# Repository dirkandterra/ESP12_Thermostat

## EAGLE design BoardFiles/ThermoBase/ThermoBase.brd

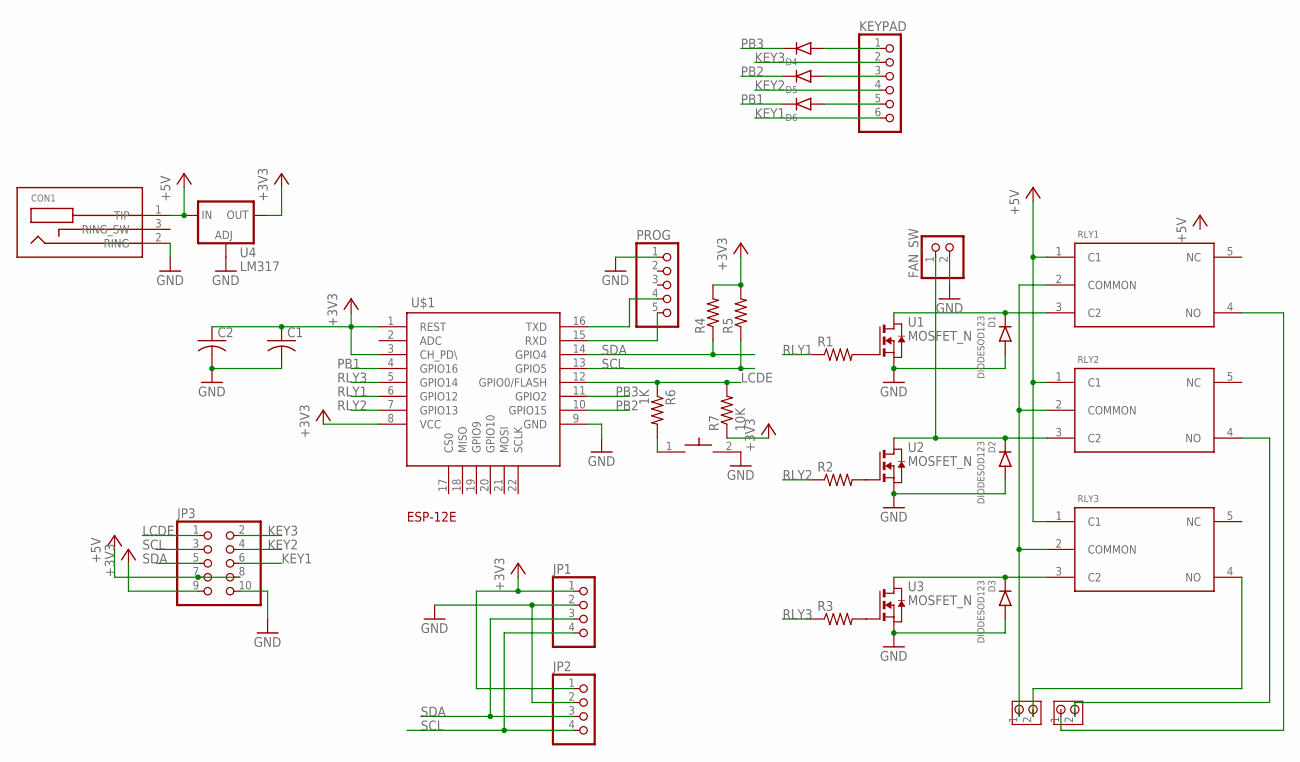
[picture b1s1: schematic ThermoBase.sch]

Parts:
BTN1: FSMSM_SWITCH_6X3.6; SMD-2-SWITCH
C1, C2: C-USC0805; C0805
CON1: BARREL_JACK_3PINPJ-102A_2MM_HOLES; PJ-102A_2MM_HOLES
D1, D2, D3, D4, D5, D6: DIODESOD123; SOD123
FAN_SW: PINHD-1X2; 1X02
H1, H2: TERMBLOCK_5MM_2POS
JP1, JP2: PINHD-1X4; 1X04
JP3: PINHD-2X5; 2X05
KEYPAD: PINHD-1X6; 1X06
PROG: PINHD-1X5; 1X05
R1, R2, R3, R4, R5: R-US_R0805; R0805
R6: 1K; R0805
R7: 10K; R0805
RLY1, RLY2, RLY3: RELAY_JQC-3F; T73_RELAY
U1, U2, U3: MOSFET_N; SOT-23
U4: LM317; SOT223
U$1: ESP-12E

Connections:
+3V3: C1.1, C2.1, JP1.1, JP2.1, JP3.9, R4.2, R5.2, R7.1, U4.2 (OUT), U4.4 (OUT), U$1.1 (REST), U$1.3 (CH_PD\), U$1.8 (VCC)
+5V: CON1.1 (TIP), JP3.7, JP3.8, RLY1.1 (C1), RLY2.1 (C1), RLY3.1 (C1), U4.3 (IN)
GND: BTN1.2, C1.2, C2.2, CON1.2 (RING), D1.1 (A), D2.1 (A), D3.1 (A), FAN_SW.2, JP1.2, JP2.2, JP3.10, PROG.1, U1.2 (S), U2.2 (S), U3.2 (S), U4.1 (ADJ), U$1.9 (GND)
KEY1: JP3.6, KEYPAD.6
KEY2: JP3.4, KEYPAD.4
KEY3: JP3.2, KEYPAD.2
LCDE: JP3.1, R6.1, R7.2, U$1.12 (GPIO0/FLASH)
unnamed: PROG.5, U$1.15 (RXD)
unnamed: PROG.4, U$1.16 (TXD)
unnamed: H2.1, RLY1.4 (NO)
unnamed: R1.2, U1.1 (G)
unnamed: R2.2, U2.1 (G)
unnamed: R3.2, U3.1 (G)
unnamed: D1.2 (C), RLY1.3 (C2), U1.3 (D)
unnamed: H2.2, RLY2.4 (NO)
unnamed: D2.2 (C), FAN_SW.1, RLY2.3 (C2), U2.3 (D)
unnamed: D3.2 (C), RLY3.3 (C2), U3.3 (D)
unnamed: H1.1, RLY1.2 (COMMON), RLY2.2 (COMMON), RLY3.2 (COMMON)
unnamed: H1.2, RLY3.4 (NO)
unnamed: D4.1 (A), KEYPAD.1
unnamed: D5.1 (A), KEYPAD.3
unnamed: D6.1 (A), KEYPAD.5
unnamed: BTN1.1, R6.2
PB1: D6.2 (C), U$1.4 (GPIO16)
PB2: D5.2 (C), U$1.10 (GPIO15)
PB3: D4.2 (C), U$1.11 (GPIO2)
RLY1: R1.1, U$1.6 (GPIO12)
RLY2: R2.1, U$1.7 (GPIO13)
RLY3: R3.1, U$1.5 (GPIO14)
SCL: JP1.4, JP2.4, JP3.3, R5.1, U$1.13 (GPIO5)
SDA: JP1.3, JP2.3, JP3.5, R4.1, U$1.14 (GPIO4)

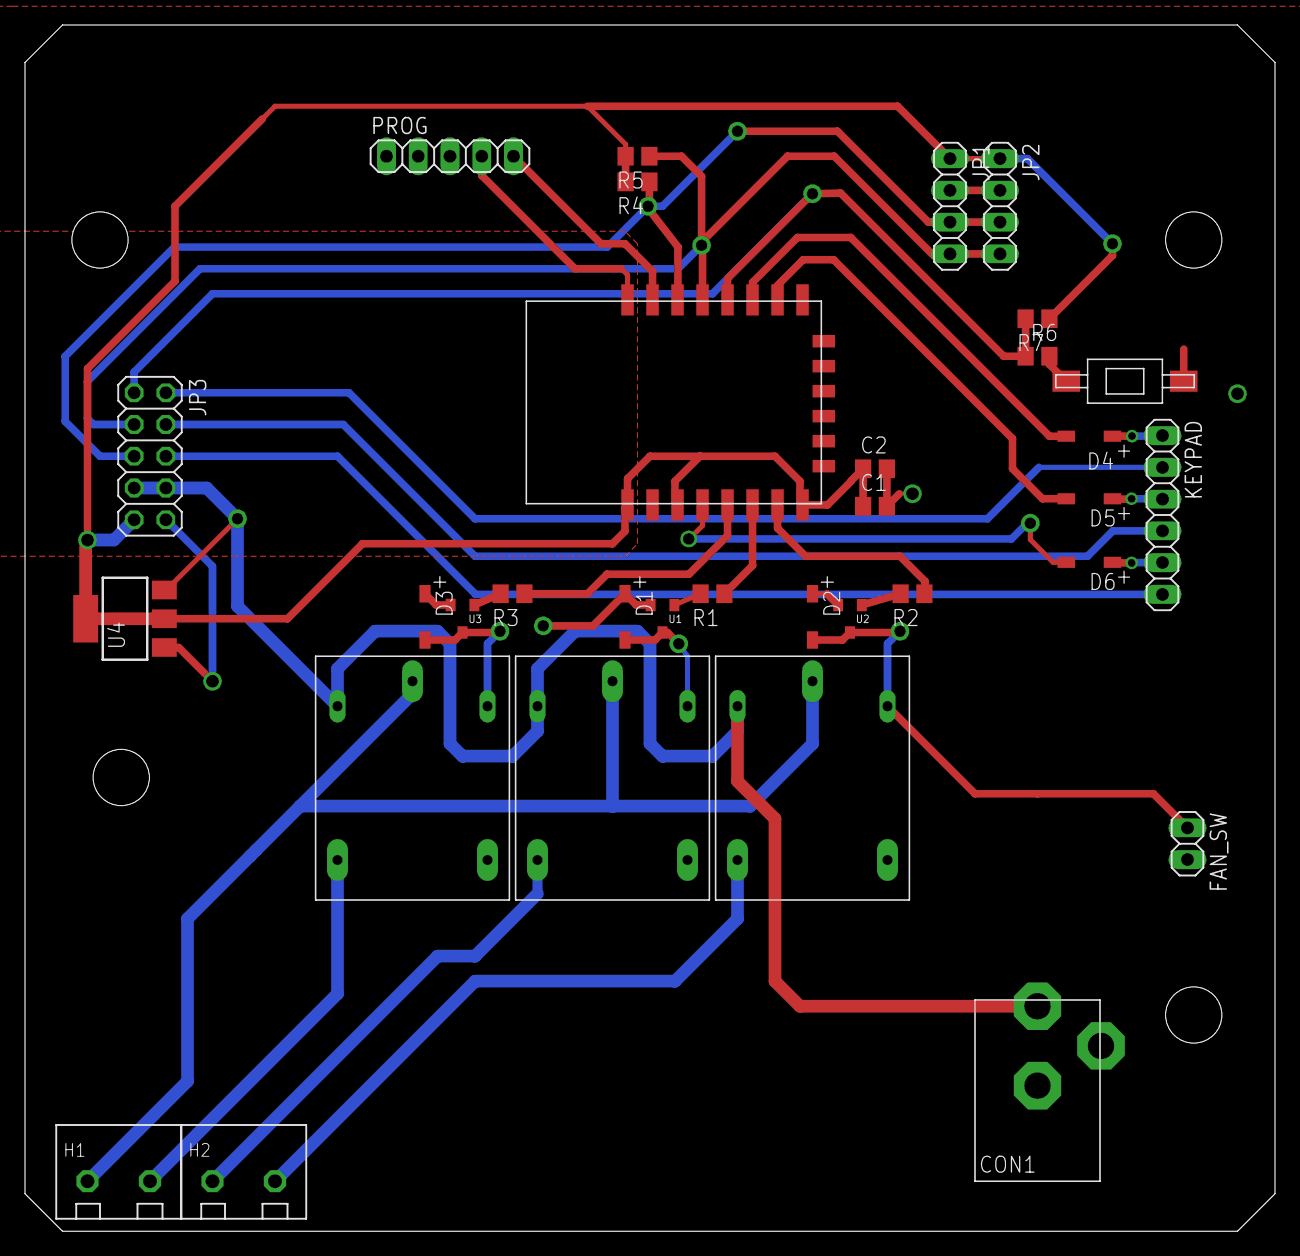
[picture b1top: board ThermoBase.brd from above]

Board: 2 copper layers, 100.0 x 96.5 mm, 33 parts (0 on the bottom side), 31 nets.

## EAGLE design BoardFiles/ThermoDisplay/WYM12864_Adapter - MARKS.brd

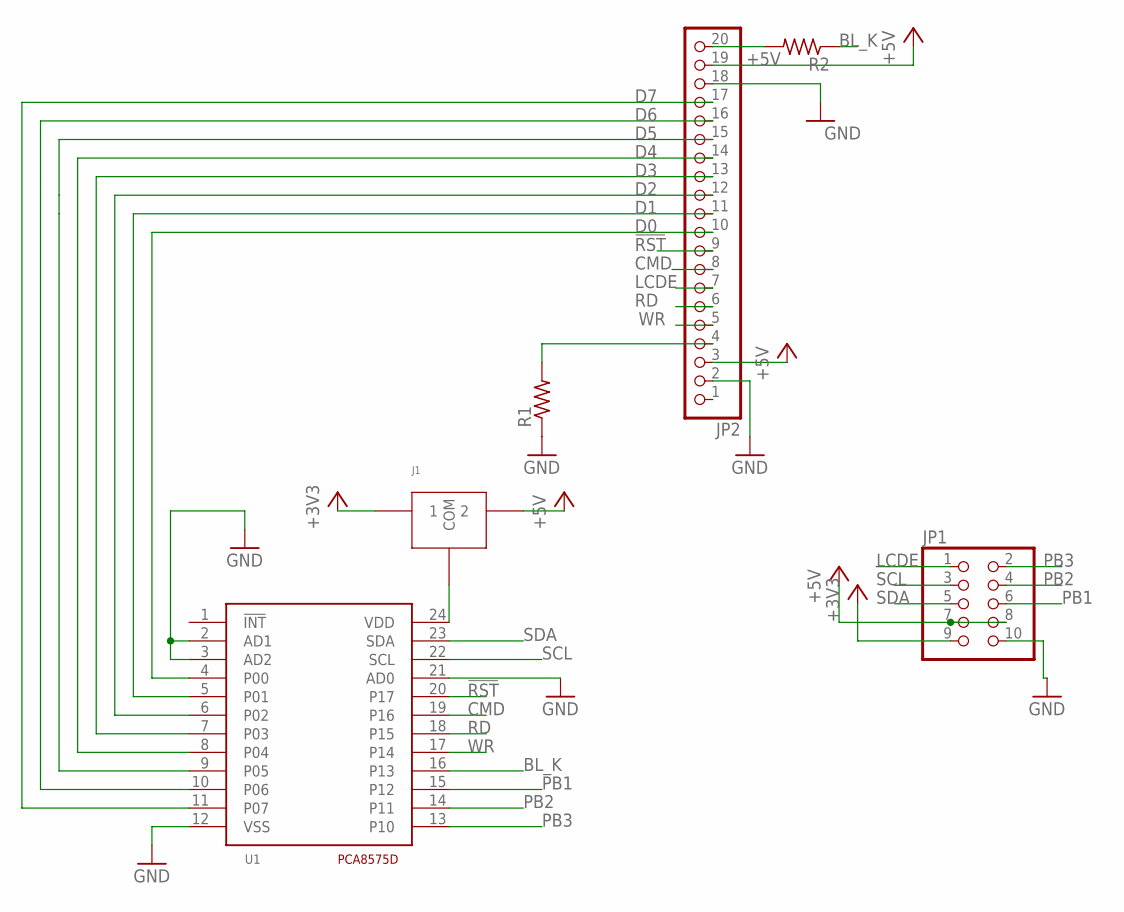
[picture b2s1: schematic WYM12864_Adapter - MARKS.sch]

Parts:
J1: JMP_3WAY; JUMPER_THREEWAY
JP1: PINHD-2X5; 2X05
JP2: PINHD-1X20; 1X20
R1, R2: R-US_M0805; M0805
U1: PCA8575DSOIC-24; SOIC-24

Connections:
!RST: JP2.9, U1.20 (P17)
+3V3: J1.1, JP1.9
+5V: J1.2, JP1.7, JP1.8, JP2.3, JP2.19
BL_K: R2.1, U1.16 (P13)
CMD: JP2.8, U1.19 (P16)
D0: JP2.10, U1.4 (P00)
D1: JP2.11, U1.5 (P01)
D2: JP2.12, U1.6 (P02)
D3: JP2.13, U1.7 (P03)
D4: JP2.14, U1.8 (P04)
D5: JP2.15, U1.9 (P05)
D6: JP2.16, U1.10 (P06)
D7: JP2.17, U1.11 (P07)
GND: JP1.10, JP2.2, JP2.18, R1.1, U1.2 (AD1), U1.3 (AD2), U1.12 (VSS), U1.21 (AD0)
LCDE: JP1.1, JP2.7
unnamed: JP2.4, R1.2
unnamed: J1.C (COM), U1.24 (VDD)
unnamed: JP2.20, R2.2
PB1: JP1.6, U1.15 (P12)
PB2: JP1.4, U1.14 (P11)
PB3: JP1.2, U1.13 (P10)
RD: JP2.6, U1.18 (P15)
SCL: JP1.3, U1.22 (SCL)
SDA: JP1.5, U1.23 (SDA)
WR: JP2.5, U1.17 (P14)

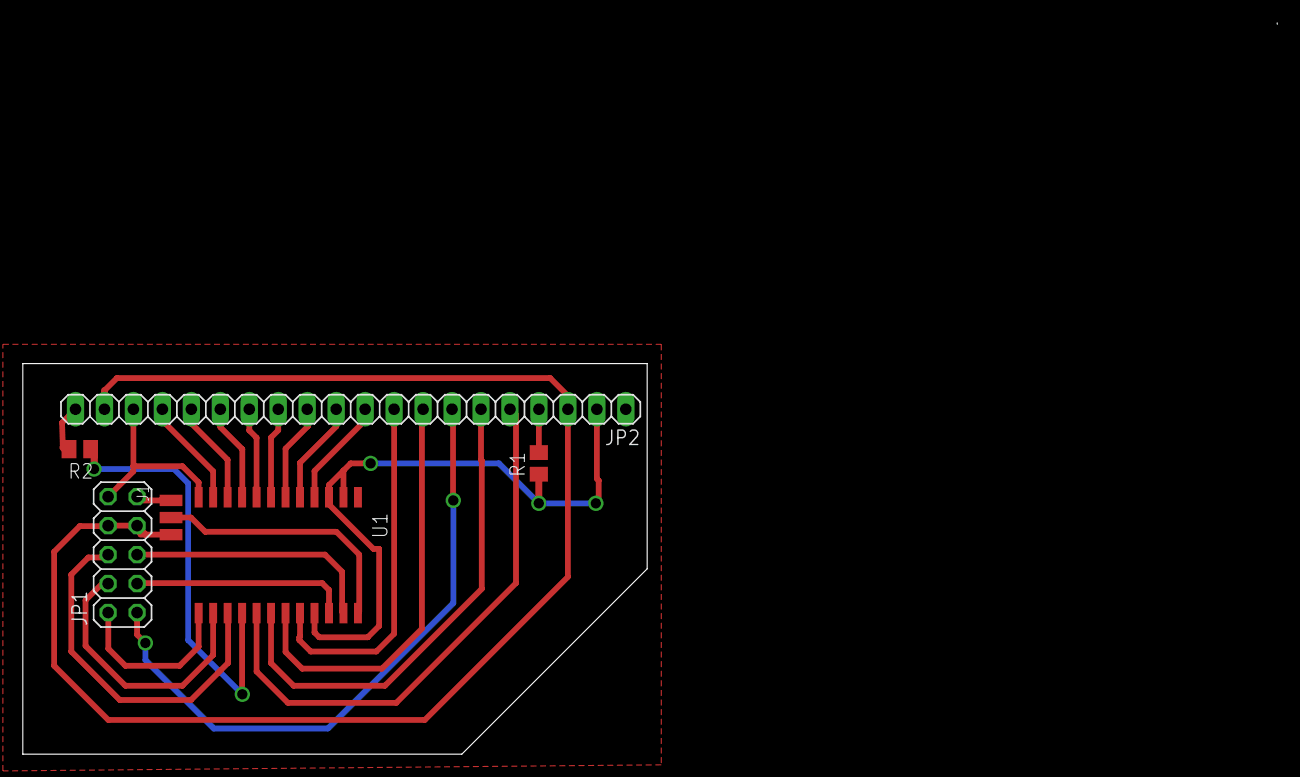
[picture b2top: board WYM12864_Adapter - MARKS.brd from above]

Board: 2 copper layers, 110.0 x 64.1 mm, 6 parts (0 on the bottom side), 25 nets.

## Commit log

2025-02-25 Some of the software
2025-02-25 Adding Thermostat test code
2025-03-02 Separated out functions into files
2025-03-04 Added SHTC3 temp, stable
2025-03-05 Added thermometer logic to ESP12_Thermostat.ino
2025-03-08 Marksman LCD test files Board files to handle PCA8575 (Ext IO)
2025-03-09 Improvements to Thermo routine
2025-03-15 Changed back to real temp instead of test
2025-03-16 Starting the base board file
2025-03-16 update to 9.6.0 eagle
2025-03-29 Save before 8575 test
2025-04-13 Fixed board schematic/board errors
2025-05-01 Created LCD Screen holder and updated base board to fit enclosure
2025-05-09 screen working with pcf8575
2025-05-14 Successfully built display board, archived old test software
2025-05-24 Few Tweaks
2025-05-24 Input changes for keypad
2025-05-24 Changes for keypad
2025-05-24 Tweaked some small leads to be bigger
2025-05-25 Getting ready for esp12 thermo on Marksman display, code compiles, still need to test
2025-05-25 Found some board errors and got an AC demo ready
2025-05-26 Made big number readout
2025-05-26 Fixing text on screen
2025-05-28 Added a MQTT message and fixed dow loading
2025-05-31 Importing screen and keys
2025-06-06 Ordered boards V1.0
